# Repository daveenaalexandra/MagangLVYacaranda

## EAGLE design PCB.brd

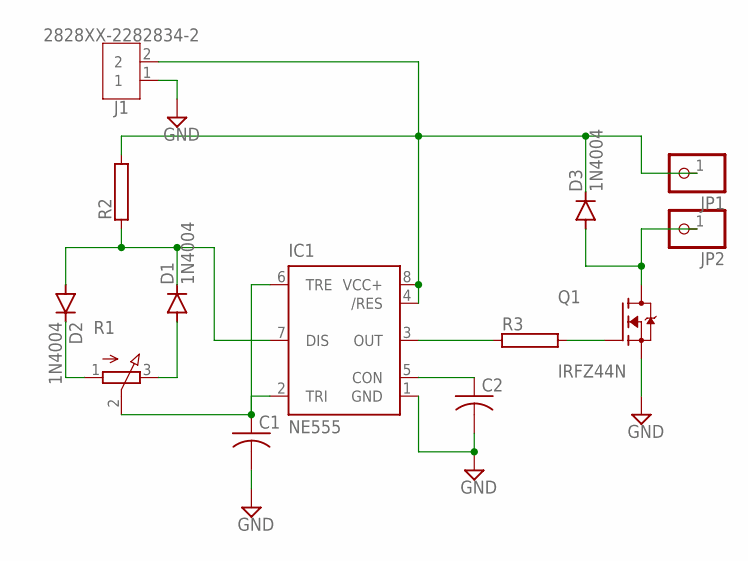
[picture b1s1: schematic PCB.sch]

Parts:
C1, C2: C-US025-024X044; C025-024X044
D1, D2, D3: 1N4004; DO41-10
IC1: NE555; DIL-08
J1: 2828XX-2282834-2; TERMBLK_254-2N
JP1, JP2: PINHD-1X1; 1X01
Q1: IRFZ44N; TO254P1016X419X2286-3
R1: 3RP/1610N
R2, R3: RAC01; AC01

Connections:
GND: C1.2, C2.2, IC1.1 (GND), J1.1, Q1.3 (S)
unnamed: D3.A, JP2.1, Q1.2 (D)
unnamed: Q1.1 (G), R3.2
unnamed: IC1.3 (OUT), R3.1
unnamed: C2.1, IC1.5 (CON)
unnamed: D1.A, R1.3 (E)
unnamed: D2.C, R1.1 (A)
unnamed: C1.1, IC1.2 (TRI), IC1.6 (TRE), R1.2 (S)
unnamed: D1.C, D2.A, IC1.7 (DIS), R2.1
unnamed: D3.C, IC1.4 (/RES), IC1.8 (VCC+), J1.2, JP1.1, R2.2

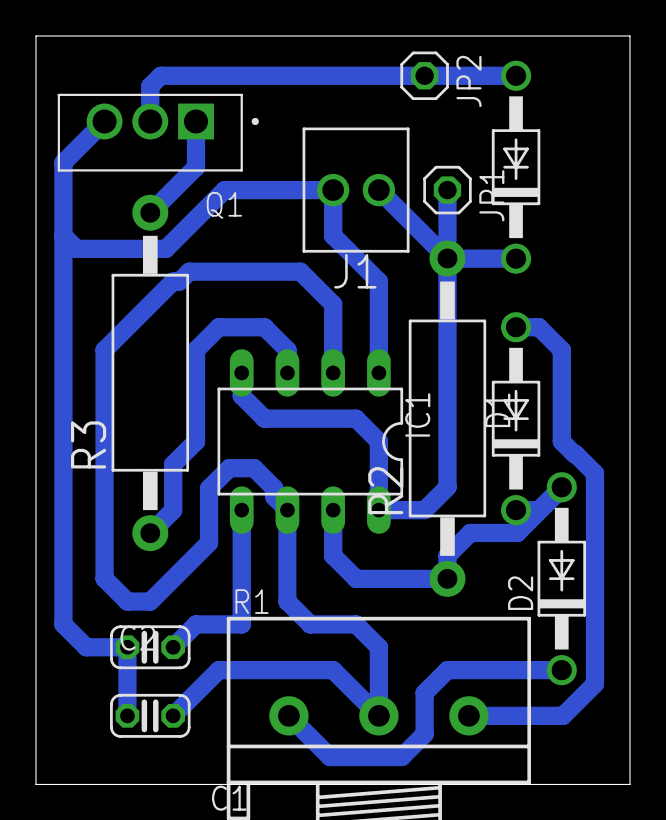
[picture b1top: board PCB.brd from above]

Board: 2 copper layers, 33.0 x 41.6 mm, 13 parts (0 on the bottom side), 10 nets.
